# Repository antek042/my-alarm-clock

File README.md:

# My-alarm-clock (Blare)

My alarm clock is my own alarm clock with a lot of modern functions! 
It uses NTP servers to get correct time, it can bring you some information like weather for today and it will do futher more!

## Features:
 - 3D printed case with holes for screen and 4 keys
 - 2.25in TFT display
 - 4 keys for setting time to wake up and navigate through the menu!

## CAD Model
The top of case and bottom fits together using 4 M3 bolts. For PCB it's also 4 M3 bolt and for the screen it's 2 M2 bolts.
It was made in Fusion360.

## PCB
The PCB was designed in KiCad. I added some 3D models to make the visualization more closely resemble how the PCB will look in the real world.
This also makes the CAD design process easier.

Schematic

PCB

## Firmware
I've used Arduino framework to make software designing process more easier.

Functions that firmware have is:
  - Menu for set alarm to wake up you!
  - Connection with NTP server through WiFi
  - In the future it will have module to present you today's weather!

## BOM
Here should be everything you need to make this alarm clock!

- 1x Seeed XIAO ESP32C3
- 1x 2.25in TFT Screen
- 1x 3.3V Piezo Buzzer
- 4x Keyboard Switches and Keycaps
- 4x 1N4148 Diodes
- 8x M3x8mm Screws
- 8x M3x5x4 Heatset Inserts
- 2x M2×3 mm Heatset Inserts
- 2x M2×3 mm Screws
- 8x 20cm Female-Female Jumper Wires
- 1x 2.54mm 8 Pin Male Header
- 1x Case ( 2 printed parts )
- 1x SMA Female to U.FL Adapter
- 1x WiFi Antena

## Extra stuff
[Here is a site where RAM prices haven't gone up](https://youtu.be/ZZ5LpwO-An4?t=2)

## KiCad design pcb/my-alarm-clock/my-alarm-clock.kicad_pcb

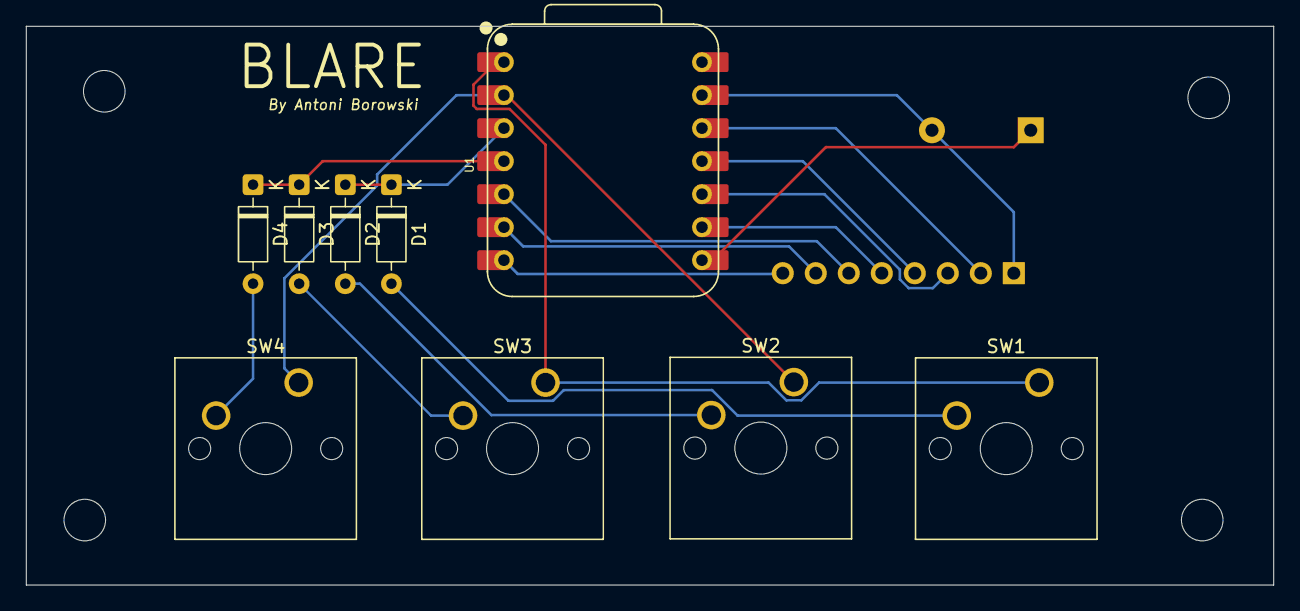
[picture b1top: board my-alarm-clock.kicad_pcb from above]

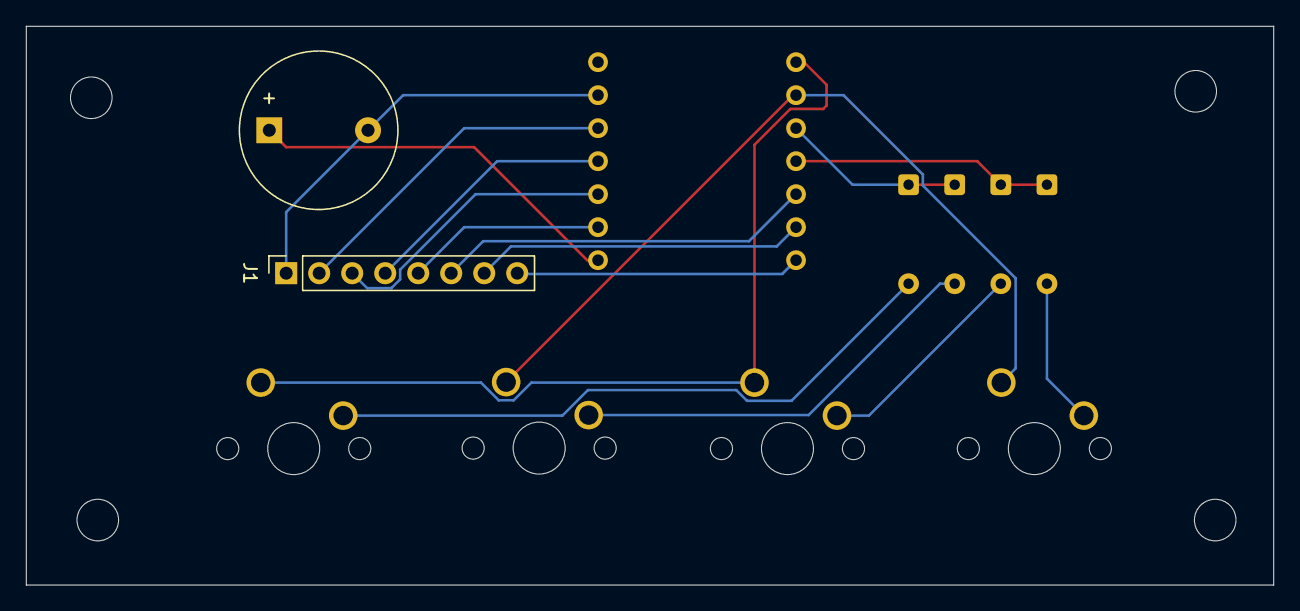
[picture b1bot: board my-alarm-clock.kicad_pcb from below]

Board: 2 copper layers, 96.0 x 43.0 mm, 15 parts (2 on the bottom side), 17 nets.

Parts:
BZ1: Buzzer; Buzzer_12x9.5RM7.6
D1, D2, D3, D4: 1N4148; D_DO-35_SOD27_P7.62mm_Horizontal
H1, H2, H3, H4: MountingHole; MountingHole_3.2mm_M3
J1: Conn_01x08_Pin; PinSocket_1x08_P2.54mm_Vertical
SW1, SW2, SW3, SW4: SW_Push; SW_Cherry_MX_1.00u_PCB
U1: XIAO-ESP32-C3-SMD; XIAO-ESP32-C3-DIP

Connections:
+3.3V: J1.2, U1.12 (3V3_OUT)
/BL: J1.8, U1.7 (D6)
/COL0: SW1.1, SW3.1, U1.1 (D0)
/COL1: SW2.1, SW4.1, U1.2 (D1)
/CS: J1.7, U1.6 (D5)
/D7_PIN: BZ1.1 (+), U1.8 (D7)
/DC: J1.6, U1.5 (D4)
/ROW0: D1.1 (K), D2.1 (K), U1.3 (D2)
/ROW1: D3.1 (K), D4.1 (K), U1.4 (D3)
/RST: J1.5, U1.9 (D8)
/SCL: J1.3, U1.10 (D9/BOOT)
/SDA: J1.4, U1.11 (D10)
GND: BZ1.2 (-), J1.1, U1.13 (GND)
unnamed: D1.2 (A), SW1.2
unnamed: D2.2 (A), SW2.2
unnamed: D3.2 (A), SW3.2
unnamed: D4.2 (A), SW4.2
